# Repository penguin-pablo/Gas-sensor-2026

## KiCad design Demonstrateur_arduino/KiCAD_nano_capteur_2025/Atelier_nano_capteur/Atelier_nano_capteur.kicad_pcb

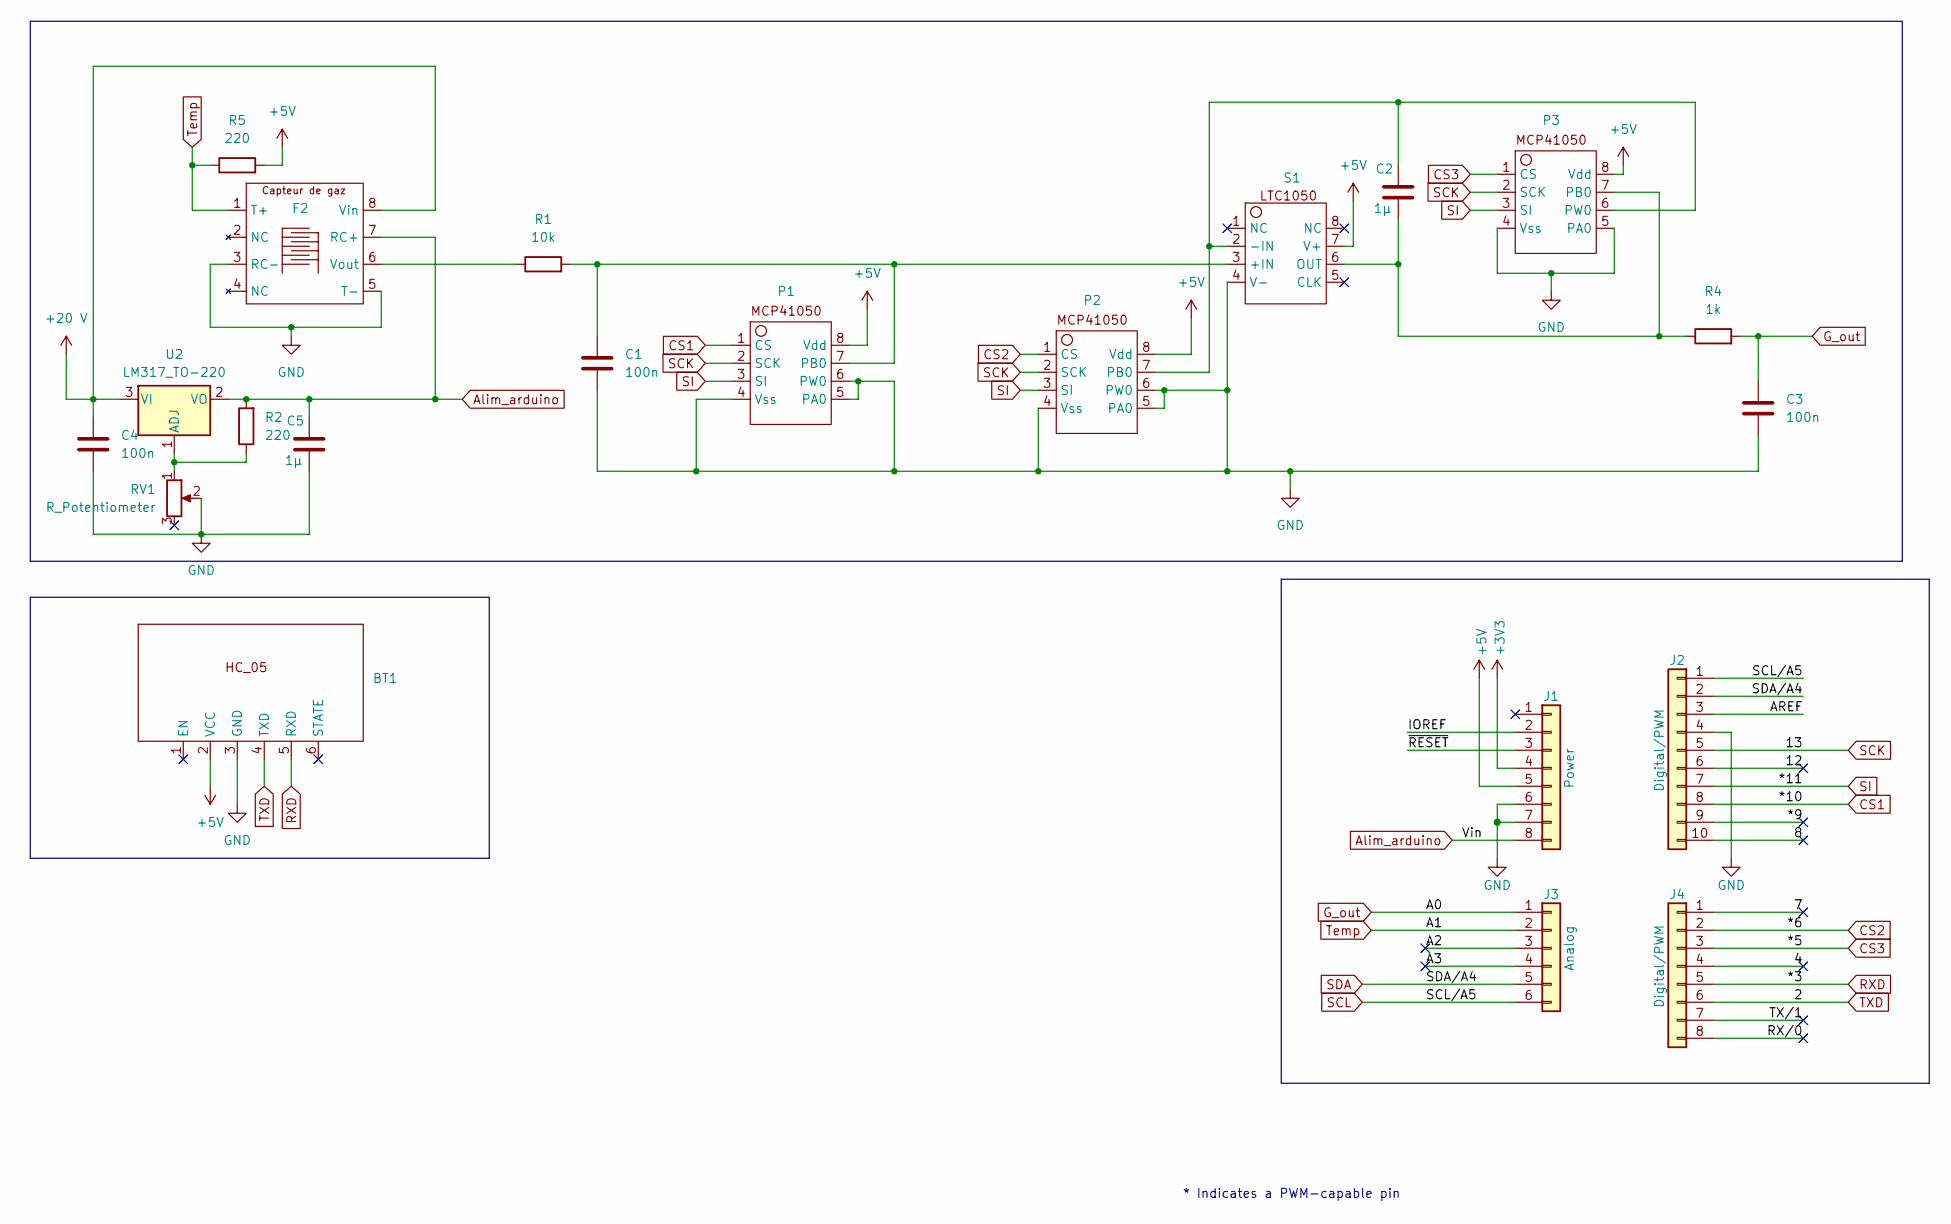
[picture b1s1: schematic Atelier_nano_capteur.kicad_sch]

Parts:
BT1: SIP-6
C1, C3, C4: 100n; C_Disc_D4.3mm_W1.9mm_P5.00mm
C2, C5: 1µ; C_Rect_L7.0mm_W4.5mm_P5.00mm
F2: Support_capteur_gaz
J1: Power; PinSocket_1x08_P2.54mm_Vertical
J2: Digital/PWM; PinSocket_1x10_P2.54mm_Vertical
J3: Analog; PinSocket_1x06_P2.54mm_Vertical
J4: Digital/PWM; PinSocket_1x08_P2.54mm_Vertical
P1, P2, P3: Support_ampli
R1: 10k; Resistance
R2, R5: 220; Resistance
R4: 1k; Resistance
RV1: R_Potentiometer; Potar
S1: Support_ampli
U2: LM317_TO-220; TO-220-3_Vertical

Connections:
+3V3: J1.4
+5V: BT1.2 (VCC), J1.5, P1.8 (Vdd), P2.8 (Vdd), P3.8 (Vdd), R5.2, S1.7 (V+)
+20 V: C4.2, F2.8 (Vin), U2.3 (VI)
/4: J4.4
/7: J4.1
/8: J2.10
/12: J2.6
/*9: J2.9
/A2: J3.3
/A3: J3.4
/AREF: J2.3
/IOREF: J1.2
/RX/0: J4.8
/TX/1: J4.7
/~RESET: J1.3
Alim_arduino: C5.1, F2.7 (RC+), J1.8, R2.2, U2.2 (VO)
CS1: J2.8, P1.1 (CS)
CS2: J4.2, P2.1 (CS)
CS3: J4.3, P3.1 (CS)
GND: BT1.3 (GND), C1.2, C3.2, C4.1, C5.2, F2.3 (RC-), F2.5 (T-), J1.6, J1.7, J2.4, P1.4 (Vss), P1.5 (PA0), P1.6 (PW0), P2.4 (Vss), P2.5 (PA0), P2.6 (PW0), P3.4 (Vss), P3.5 (PA0), RV1.2, S1.4 (V-)
G_out: C3.1, J3.1, R4.2
unnamed: F2.6 (Vout), R1.1
unnamed: C1.1, P1.7 (PB0), R1.2, S1.3 (+IN)
unnamed: C2.1, P2.7 (PB0), P3.6 (PW0), S1.2 (-IN)
unnamed: C2.2, P3.7 (PB0), R4.1, S1.6 (OUT)
unnamed: R2.1, RV1.1, U2.1 (ADJ)
RXD: BT1.5 (RXD), J4.5
SCK: J2.5, P1.2 (SCK), P2.2 (SCK), P3.2 (SCK)
SCL: J2.1, J3.6
SDA: J2.2, J3.5
SI: J2.7, P1.3 (SI), P2.3 (SI), P3.3 (SI)
TXD: BT1.4 (TXD), J4.6
Temp: F2.1 (T+), J3.2, R5.1

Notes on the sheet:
* Indicates a PWM-capable pin

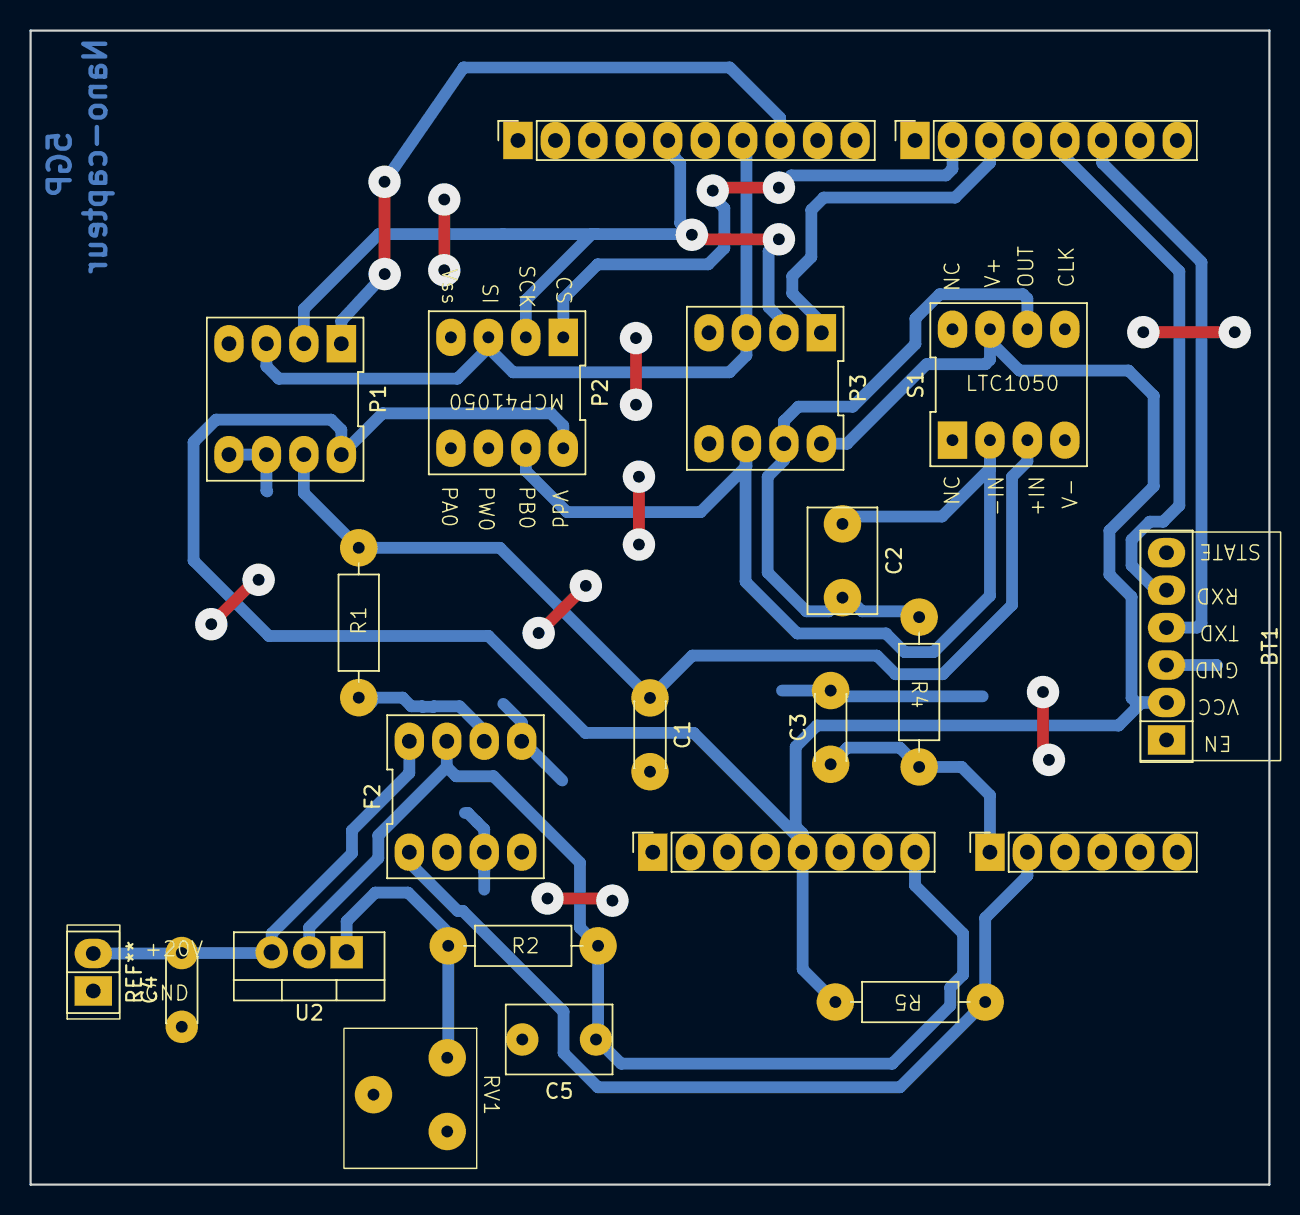
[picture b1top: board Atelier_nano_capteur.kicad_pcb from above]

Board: 2 copper layers, 84.0 x 78.2 mm, 21 parts (0 on the bottom side), 20 nets.
